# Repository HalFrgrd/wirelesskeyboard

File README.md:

---
layout: default
title: Wireless keyboard project
has_children: true
---

## Wireless keyboard

Resources for making a wireless keyboard.
Also general electronics resources.

- [Unnamed 40% keyboard](60_case_keyboard/README.md)

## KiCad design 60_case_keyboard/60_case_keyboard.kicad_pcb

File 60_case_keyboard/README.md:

---
layout: default
title: Unnamed keyboard
parent: Wireless keyboard project
---

# Unnamed keyboard
A PCB to fit into the 60% keyboard case I have.
- 35%
- Wireless
- Low power LCD
- Buzzer
- Rotary encoder
- Electronics based on the [nrfmicro](https://github.com/joric/nrfmicro/).

### LCD Notes
https://makerdyne.com/2015/02/08/large-memory-lcd-breakout-board-details/

The power supply input is 5V. 
But the logic levels are all 3.3V.

### Footprints
https://github.com/daprice/keyswitches.pretty

### Dimensions
These are some dimensions of [the specific case I used.](https://www.aliexpress.com/item/32921993410.html?pid=808_0000_0101&spm=a2g0n.search-amp.list.32921993410&aff_trace_key=2b17650114d94b82bf89c85dab72a30e-1550938224177-03600-UneMJZVf&aff_platform=msite&m_page_id=6878amp-RE3tNnzZA5LCyChfdei61Q1552019685186)

- Case to standoff: 4.6mm
- Indented case to standoff: 7.0mm
- LCD connector height: 1.8mm
- Distance from edge of case to LCD connector: 50.0mm
- Useable indentation width: 42.1mm
- Useable indentation length: 145.0mm
- Useable indentation length with drop through rotary encoder: 109.0mm
- Useable case width: 90.0mm

### Flashing
These are based on the instructions found in [joric's nrfmicro](https://github.com/joric/nrfmicro/wiki/Bootloader).

#### ST-Link V2 converted to Black Magic Probe
I used two ST-Link/V2 clone's and converted one into a [Black Magic Probe](https://github.com/blacksphere/blackmagic) using the instructions found [here](https://web.archive.org/web/20210121183153/http://blog.linuxbits.io/2016/02/15/cheap-chinese-st-link-v-2-programmer-converted-to-black-magic-probe-debugger/).
My notes on the conversion process are [here](https://github.com/HalFrgrd/halfrgrd.github.io/blob/master/black_magic_probe_windows_mingw64.md).
I would recommend this route as the two ST-Link V2 clone's will cost less than $5.

#### Flashing notes
[GDB (GNU Project Debugger)](https://www.gnu.org/software/gdb/) is used to control the Black Magic Probe.
When I ran `target extended-remote COM3`, it'd hang or give an error. 
This was on Windows 10.
I found I could get working on Ubuntu 18.04 using `gdb-multiarch`.
I had to hold down the wires on the keyboard for the scanning to pick up the nrf52.

I ran the code command by command instead of the two lines joric gives.
For reference, the output of the gdb process is as follows:
```
(gdb) target extended-remote /dev/ttyACM0
Remote debugging using /dev/ttyACM0
(gdb) monitor swdp_scan
Target voltage: 3.28V
SW-DP scan failed!
(gdb) monitor swdp_scan
Target voltage: 3.28V
Available Targets:
No. Att Driver
 1      Nordic nRF52 M3/M4
 2      Nordic nRF52 Access Port
(gdb) att 1
Attaching to Remote target
warning: while parsing target description (at line 1): Target description specified unknown architecture "arm"
warning: Could not load XML target description; ignoring
Truncated register 34 in remote 'g' packet
(gdb) Truncated register 34 in remote 'g' packet
(gdb) mon erase_mass
erase..
Truncated register 34 in remote 'g' packet
(gdb) file ~/Downloads/bootloader.hex
A program is being debugged already.
Are you sure you want to change the file? (y or n) y
Reading symbols from ~/Downloads/bootloader.hex...(no debugging symbols found)...done.
Truncated register 34 in remote 'g' packet
(gdb) att 1
A program is being debugged already.  Kill it? (y or n) y
Attaching to program: /home/hfrgrd/Downloads/bootloader.hex, Remote target
warning: while parsing target description (at line 1): Target description specified unknown architecture "arm"
warning: Could not load XML target description; ignoring
Truncated register 34 in remote 'g' packet
(gdb) Truncated register 34 in remote 'g' packet
(gdb) mon erase
erase..
Truncated register 34 in remote 'g' packet
(gdb) load
Loading section .sec1, size 0xb00 lma 0x0
Loading section .sec2, size 0xf000 lma 0x1000
Loading section .sec3, size 0x10000 lma 0x10000
Loading section .sec4, size 0x5de8 lma 0x20000
Loading section .sec5, size 0x70c8 lma 0xf4000
Loading section .sec6, size 0x8 lma 0x10001014
Start address 0x0, load size 182712
Truncated register 34 in remote 'g' packet
```

arm-none-eabi-gdb.exe --batch -ex "target extended-remote \\.\COM5" -ex "mon swdp_scan" -ex "att 1" -ex "mon erase_mass"

arm-none-eabi-gdb.exe --batch -ex "target extended-remote \\.\COM5" -ex "mon swdp_scan" -ex "file C:/Users/hal/Documents/Github/wirelesskeyboard/60_case_keyboard/bootloader.hex" -ex "att 1" -ex "mon erase" -ex load

Github:

CIRCUITPY still shows up. I can change code.py 

rows x cols grid
2x2: stable
2x5: stable
2x10: hangs

2x6 with 0.01 secs sleep: stable
2x6 with 0.001 secs sleep: hangs
2x2 with 0.001 secs sleep: hangs

**Solution:** when I commented out the sleep line, it works fine!
It seems to get caught in sleep which would make sense.

This is similar: https://github.com/adafruit/circuitpython/issues/3829

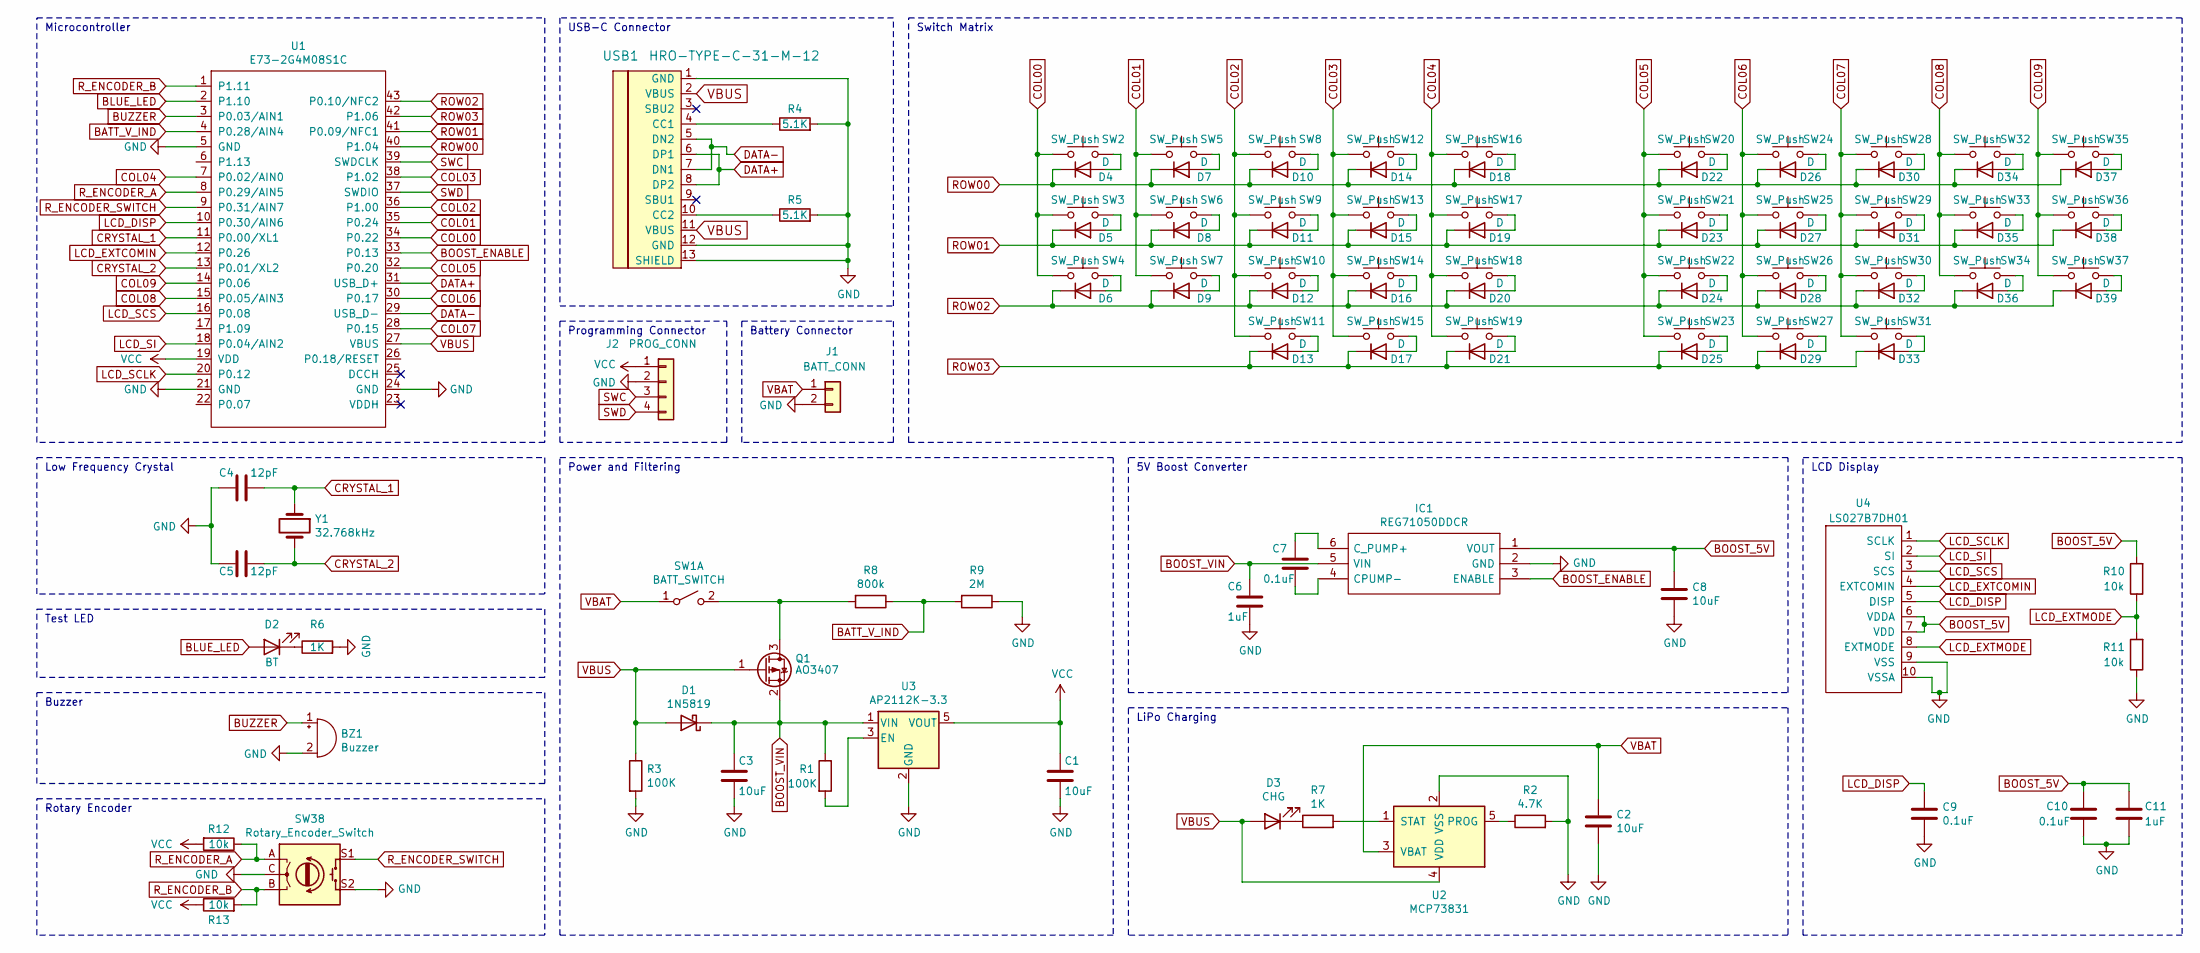
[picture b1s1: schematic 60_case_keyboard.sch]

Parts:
BZ1: Buzzer; Buzzer_12x9.5RM7.6
C1, C2, C3, C8: 10uF; C_1206_3216Metric_Pad1.42x1.75mm_HandSolder
C4, C5: 12pF; C_1206_3216Metric_Pad1.42x1.75mm_HandSolder
C6, C11: 1uF; C_1206_3216Metric_Pad1.42x1.75mm_HandSolder
C7, C9, C10: 0.1uF; C_1206_3216Metric_Pad1.42x1.75mm_HandSolder
D1: 1N5819; D_SOD-123
D2: BT; LED_0603_1608Metric
D3: CHG; LED_0603_1608Metric
D4, D5, D6, D7, D8, D9, D10, D11, D12, D13, D14, D15, D16, D17, D18, D19, D20, D21, D22, D23, D24, D25, D26, D27, D28, D29, D30, D31, D32, D33, D34, D35, D36, D37, D38, D39: D; D_DO-35_SOD27_P7.62mm_Horizontal
IC1: REG71050DDCR; SOT95P280X110-6N; Mouser Part Number 595-REG71050DDCR
J1: BATT_CONN; JST_EH_S2B-EH_1x02_P2.50mm_Horizontal
J2: PROG_CONN; PinHeader_1x04_P2.54mm_Vertical
Q1: AO3407; SOT-23
R1, R3: 100K; R_Axial_DIN0204_L3.6mm_D1.6mm_P5.08mm_Horizontal
R2: 4.7K; R_Axial_DIN0204_L3.6mm_D1.6mm_P5.08mm_Horizontal
R4, R5: 5.1K; R_Axial_DIN0204_L3.6mm_D1.6mm_P5.08mm_Horizontal
R6, R7: 1K; R_Axial_DIN0204_L3.6mm_D1.6mm_P5.08mm_Horizontal
R8: 800k; R_Axial_DIN0204_L3.6mm_D1.6mm_P5.08mm_Horizontal
R9: 2M; R_Axial_DIN0204_L3.6mm_D1.6mm_P5.08mm_Horizontal
R10, R11, R12, R13: 10k; R_Axial_DIN0204_L3.6mm_D1.6mm_P5.08mm_Horizontal
SW1: BATT_SWITCH; MSK-12D19_Sliding_Switch
SW2, SW3, SW4, SW5, SW6, SW7, SW8, SW9, SW10, SW11, SW12, SW13, SW14, SW15, SW16, SW17, SW18, SW19, SW20, SW21, SW22, SW23, SW24, SW25, SW26, SW27, SW28, SW29, SW30, SW31, SW32, SW33, SW34, SW35, SW36, SW37: SW_Push; SW_PG1350_reversible
SW38: Rotary_Encoder_Switch; RotaryEncoder_Alps_EC11E-Switch_Vertical_H20mm
U1: E73-2G4M08S1C; E73-2G4M08S1C-52840_with_breakout
U2: MCP73831; SOT-23-5
U3: AP2112K-3.3; SOT-23-5
U4: LS027B7DH01; 0527451033_flipped
USB1: HRO-TYPE-C-31-M-12
Y1: 32.768kHz; Crystal_DS26_D2.0mm_L6.0mm_Horizontal

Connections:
BATT_V_IND: R8.1, R9.2, U1.4 (P0.28/AIN4)
BLUE_LED: D2.2 (A), U1.2 (P1.10)
BOOST_5V: C8.1, C10.1, C11.1, IC1.1 (VOUT), R10.2, U4.6 (VDDA), U4.7 (VDD)
BOOST_ENABLE: IC1.3 (ENABLE), U1.33 (P0.13)
BOOST_VIN: C3.1, C6.1, D1.1 (K), IC1.5 (VIN), Q1.2 (S), R1.1, U3.1 (VIN)
BUZZER: BZ1.1 (-), U1.3 (P0.03/AIN1)
COL00: SW2.1, SW3.1, SW4.1, U1.34 (P0.22)
COL01: SW5.1, SW6.1, SW7.1, U1.35 (P0.24)
COL02: SW8.1, SW9.1, SW10.1, SW11.1, U1.36 (P1.00)
COL03: SW12.1, SW13.1, SW14.1, SW15.1, U1.38 (P1.02)
COL04: SW16.1, SW17.1, SW18.1, SW19.1, U1.7 (P0.02/AIN0)
COL05: SW20.1, SW21.1, SW22.1, SW23.1, U1.32 (P0.20)
COL06: SW24.1, SW25.1, SW26.1, SW27.1, U1.30 (P0.17)
COL07: SW28.1, SW29.1, SW30.1, SW31.1, U1.28 (P0.15)
COL08: SW32.1, SW33.1, SW34.1, U1.15 (P0.05/AIN3)
COL09: SW35.1, SW36.1, SW37.1, U1.14 (P0.06)
CRYSTAL_1: C4.1, U1.11 (P0.00/XL1), Y1.1
CRYSTAL_2: C5.1, U1.13 (P0.01/XL2), Y1.2
DATA+: U1.31 (USB_D+), USB1.6 (DP1), USB1.8 (DP2)
DATA-: U1.29 (USB_D-), USB1.5 (DN2), USB1.7 (DN1)
GND: BZ1.2 (+), C1.2, C2.2, C3.2, C4.2, C5.2, C6.2, C8.2, C9.2, C10.2, C11.2, IC1.2 (GND), J1.2, J2.2, R2.2, R3.2, R4.2, R5.2, R6.2, R9.1, R11.1, SW38.C, SW38.S2, U1.5 (GND), U1.21 (GND), U1.24 (GND), U2.2 (VSS), U3.2 (GND), U4.9 (VSS), U4.10 (VSSA), USB1.1 (GND), USB1.12 (GND), USB1.13 (SHIELD)
LCD_DISP: C9.1, U1.10 (P0.30/AIN6), U4.5 (DISP)
LCD_EXTCOMIN: U1.12 (P0.26), U4.4 (EXTCOMIN)
LCD_EXTMODE: R10.1, R11.2, U4.8 (EXTMODE)
LCD_SCLK: U1.20 (P0.12), U4.1 (SCLK)
LCD_SCS: U1.16 (P0.08), U4.3 (SCS)
LCD_SI: U1.18 (P0.04/AIN2), U4.2 (SI)
unnamed: C7.1, IC1.6 (C_PUMP+)
unnamed: C7.2, IC1.4 (CPUMP-)
unnamed: D2.1 (K), R6.1
unnamed: D3.1 (K), R7.1
unnamed: D4.2 (A), SW2.2
unnamed: D5.2 (A), SW3.2
unnamed: D6.2 (A), SW4.2
unnamed: D7.2 (A), SW5.2
unnamed: D8.2 (A), SW6.2
unnamed: D9.2 (A), SW7.2
unnamed: D10.2 (A), SW8.2
unnamed: D11.2 (A), SW9.2
unnamed: D12.2 (A), SW10.2
unnamed: D13.2 (A), SW11.2
unnamed: D14.2 (A), SW12.2
unnamed: D15.2 (A), SW13.2
unnamed: D16.2 (A), SW14.2
unnamed: D17.2 (A), SW15.2
unnamed: D18.2 (A), SW16.2
unnamed: D19.2 (A), SW17.2
unnamed: D20.2 (A), SW18.2
unnamed: D21.2 (A), SW19.2
unnamed: D22.2 (A), SW20.2
unnamed: D23.2 (A), SW21.2
unnamed: D24.2 (A), SW22.2
unnamed: D25.2 (A), SW23.2
unnamed: D26.2 (A), SW24.2
unnamed: D27.2 (A), SW25.2
unnamed: D28.2 (A), SW26.2
unnamed: D29.2 (A), SW27.2
unnamed: D30.2 (A), SW28.2
unnamed: D31.2 (A), SW29.2
unnamed: D32.2 (A), SW30.2
unnamed: D33.2 (A), SW31.2
unnamed: D34.2 (A), SW32.2
unnamed: D35.2 (A), SW33.2
unnamed: D36.2 (A), SW34.2
unnamed: D37.2 (A), SW35.2
unnamed: D38.2 (A), SW36.2
unnamed: D39.2 (A), SW37.2
unnamed: Q1.3 (D), R8.2, SW1.2 (B)
unnamed: R1.2, U3.3 (EN)
unnamed: R2.1, U2.5 (PROG)
unnamed: R4.1, USB1.4 (CC1)
unnamed: R5.1, USB1.10 (CC2)
unnamed: R7.2, U2.1 (STAT)
ROW00: D4.1 (K), D7.1 (K), D10.1 (K), D14.1 (K), D18.1 (K), D22.1 (K), D26.1 (K), D30.1 (K), D34.1 (K), D37.1 (K), U1.40 (P1.04)
ROW01: D5.1 (K), D8.1 (K), D11.1 (K), D15.1 (K), D19.1 (K), D23.1 (K), D27.1 (K), D31.1 (K), D35.1 (K), D38.1 (K), U1.41 (P0.09/NFC1)
ROW02: D6.1 (K), D9.1 (K), D12.1 (K), D16.1 (K), D20.1 (K), D24.1 (K), D28.1 (K), D32.1 (K), D36.1 (K), D39.1 (K), U1.43 (P0.10/NFC2)
ROW03: D13.1 (K), D17.1 (K), D21.1 (K), D25.1 (K), D29.1 (K), D33.1 (K), U1.42 (P1.06)
R_ENCODER_A: R12.1, SW38.A, U1.8 (P0.29/AIN5)
R_ENCODER_B: R13.2, SW38.B, U1.1 (P1.11)
R_ENCODER_SWITCH: SW38.S1, U1.9 (P0.31/AIN7)
SWC: J2.3, U1.39 (SWDCLK)
SWD: J2.4, U1.37 (SWDIO)
VBAT: C2.1, J1.1, SW1.1 (A), U2.3 (VBAT)
VBUS: D1.2 (A), D3.2 (A), Q1.1 (G), R3.1, U1.27 (VBUS), U2.4 (VDD), USB1.2 (VBUS), USB1.11 (VBUS)
VCC: C1.1, J2.1, R12.2, R13.1, U1.19 (VDD), U3.5 (VOUT)

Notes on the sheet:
LiPo Charging
Rotary Encoder
Buzzer
Test LED
Low Frequency Crystal
Microcontroller
USB-C Connector
Programming Connector
Battery Connector
Switch Matrix
Power and Filtering
5V Boost Converter
LCD Display

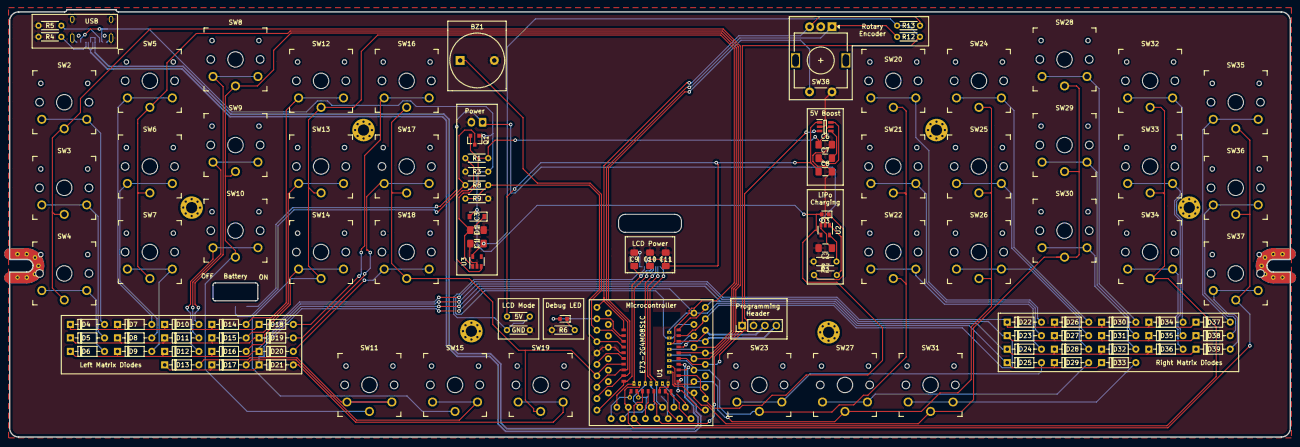
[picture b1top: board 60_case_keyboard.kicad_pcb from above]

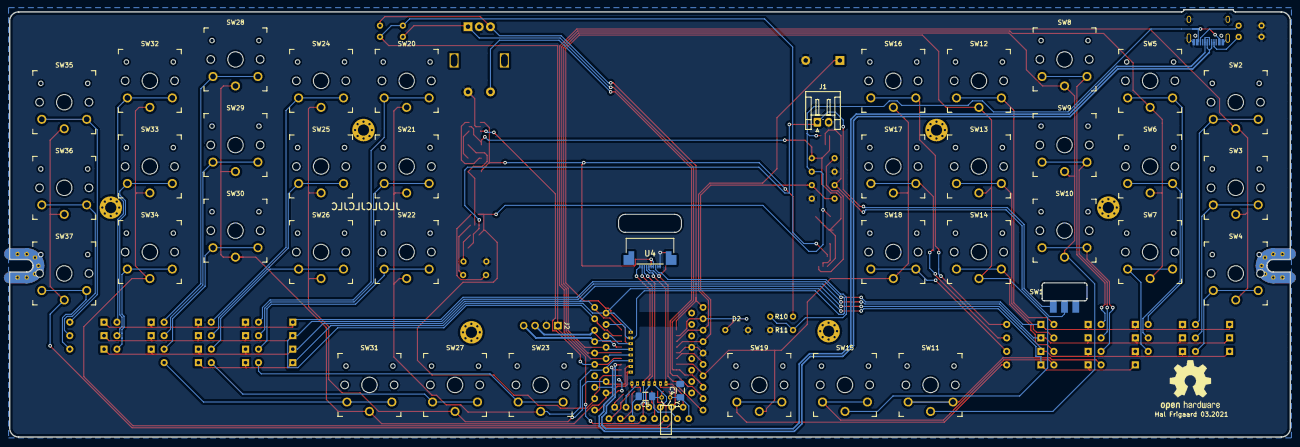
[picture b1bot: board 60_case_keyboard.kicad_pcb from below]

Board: 2 copper layers, 285.0 x 95.1 mm, 112 parts (7 on the bottom side), 85 nets.

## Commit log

2020-06-09 Set theme jekyll-theme-minimal
2020-06-09 started pages
2020-06-09 added electronics resources
2020-06-09 fixed some links
2020-06-09 added other builds
2020-06-10 testing maths
2020-06-10 Added more stuff
2020-06-10 Some more
2020-06-11 restructured
2020-06-11 Added nrfmicro as submodule
2020-06-11 Changed submodule to my fork of it
2020-06-12 asdasd
2020-06-25 Added some more stuff
2021-03-27 Added 60% keyboard design
2021-03-27 Some changes
2021-03-27 Set theme jekyll-theme-hacker
2021-04-16 Info on flashing
2021-04-18 changing to parent
2021-04-24 symbol layer
2024-12-08 moved notes to obsidian
